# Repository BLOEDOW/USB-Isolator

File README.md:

# USB-Isolator
USB port isolator based on an [Analog Devices ADuM3160](http://www.analog.com/en/interface-isolation/digital-isolators/adum3160/products/product.html) to protect computers against over-voltage spikes, ESD pulses and to avoid ground loops.

## Shop
* [USB-Isolator](http://www.watterott.com/en/USB-Isolator) (galvanic isolated Low/Full Speed USB)
* Suitable Enclosure: [Teko SOAP 1 10006/2](http://www.watterott.com/en/Teko-SOAP1-10006-2-5)

## Features
* USB 2.0 compatible
* Full Speed (12 Mbps, default setting) and Low Speed (1.5 Mbps) switchable via soldering Jumper (typical low speed devices are keyboards, mice)
* Upstream short-circuit protection
* Built-in DC-DC converter (up to 400mA output current on Host side)
* Based on Analog Devices ADuM3160
* USB-Device: microUSB
* USB-Host: USB-A

## Hardware
* [Schematics + Layout](https://github.com/watterott/USB-Isolator/tree/master/hardware)

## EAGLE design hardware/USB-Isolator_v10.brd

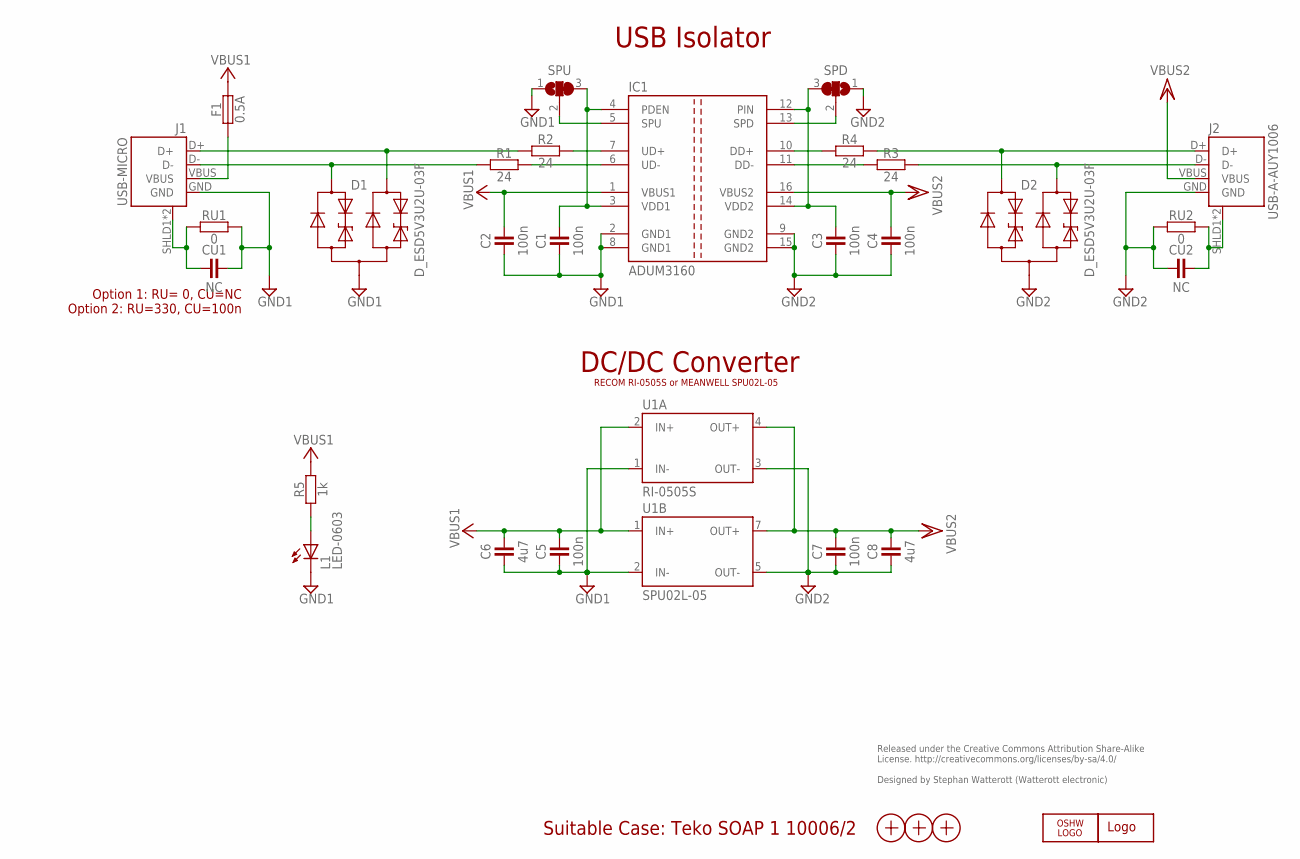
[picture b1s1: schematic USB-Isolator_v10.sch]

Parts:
C1, C2, C3, C4, C5, C7: 100n; R0603
C6, C8: 4u7; R1206
CU1, CU2: NC; R0603
D1, D2: D_ESD5V3U2U-03F; TSFP3
F1: 0.5A; R0805
IC1: ADUM3160; SO16W
J1: USB-MICRO; USB-MICRO-10103594
J2: USB-A-AUY1006; USB-AU-Y1006-R
L1: LED-0603; LED_0603
LOGO2: OSHW_LOGOX0070; OSHW_6X70
LOGO3: LOGO-S_PLACE_M; SPARK_TPLACE_M
R1, R2, R3, R4: 24; R0603
R5: 1k; R0603
RU1, RU2: 0; R0603
SPD: JUMPER3
SPU: JUMPER3
U1A: RI-0505S; RECOM_SIP4_RI
U1B: SPU02L-05; MEANWELL_SIP7_SPU02
X1, X2, X3: PASSER-07; PASSER_07MM

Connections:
D1_N: D1.1 (C1), J1.D-, R1.1
D1_P: D1.2 (C2), J1.D+, R2.1
D2_N: D2.2 (C2), J2.D-, R3.2
D2_P: D2.1 (C1), J2.D+, R4.2
DD+: IC1.10 (DD+), R4.1
DD-: IC1.11 (DD-), R3.1
GND1: C1.1, C2.1, C5.1, C6.1, CU1.2, D1.3 (A), IC1.2 (GND1), IC1.8 (GND1), J1.GND, L1.C, RU1.2, SPU.1, U1A.1 (IN-), U1B.2 (IN-)
GND2: C3.1, C4.1, C7.1, C8.1, CU2.1, D2.3 (A), IC1.9 (GND2), IC1.15 (GND2), J2.GND, RU2.1, SPD.1, U1A.3 (OUT-), U1B.5 (OUT-)
LED: L1.A, R5.1
SHLD1: CU1.1, J1.SHLD1 (SHIELD), J1.SHLD2 (SHIELD), RU1.1
SHLD2: CU2.2, J2.SHLD1 (SHIELD), J2.SHLD2 (SHIELD), RU2.2
SPD: IC1.13 (SPD), SPD.2
SPU: IC1.5 (SPU), SPU.2
UD+: IC1.7 (UD+), R2.2
UD-: IC1.6 (UD-), R1.2
VBUS1: C2.2, C5.2, C6.2, F1.2, IC1.1 (VBUS1), R5.2, U1A.2 (IN+), U1B.1 (IN+)
VBUS1A: F1.1, J1.VBUS
VBUS2: C4.2, C7.2, C8.2, IC1.16 (VBUS2), J2.VBUS, U1A.4 (OUT+), U1B.7 (OUT+)
VDD1: C1.2, IC1.3 (VDD1), IC1.4 (PDEN), SPU.3
VDD2: C3.2, IC1.12 (PIN), IC1.14 (VDD2), SPD.3

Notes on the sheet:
Suitable Case: Teko SOAP 1 10006/2
Released under the Creative Commons Attribution Share-Alike License. http://creativecommons.org/licenses/by-sa/4.0/ Designed by Stephan Watterott (Watterott electronic)
DC/DC Converter
USB Isolator
Option 1: RU= 0, CU=NC Option 2: RU=330, CU=100n
RECOM RI-0505S or MEANWELL SPU02L-05

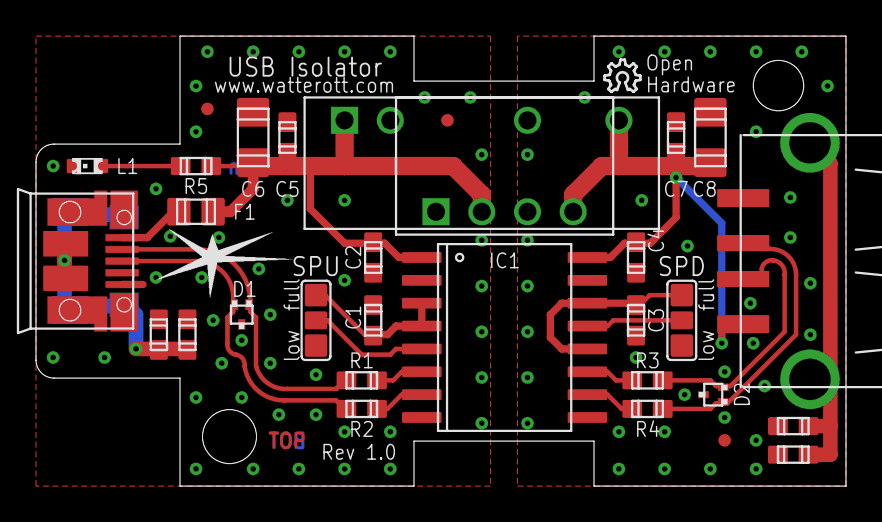
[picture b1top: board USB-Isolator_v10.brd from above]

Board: 2 copper layers, 45.0 x 25.0 mm, 33 parts (0 on the bottom side), 20 nets.

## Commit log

2014-08-29 added image
2014-08-29 added layout and schematics
2014-09-16 updated layout and schematics
2014-11-03 updated schematics
2014-11-06 cleaned up schematics and layout
2015-01-11 moved image
2015-08-21 changed path structure
2016-06-09 added rev 1.1
